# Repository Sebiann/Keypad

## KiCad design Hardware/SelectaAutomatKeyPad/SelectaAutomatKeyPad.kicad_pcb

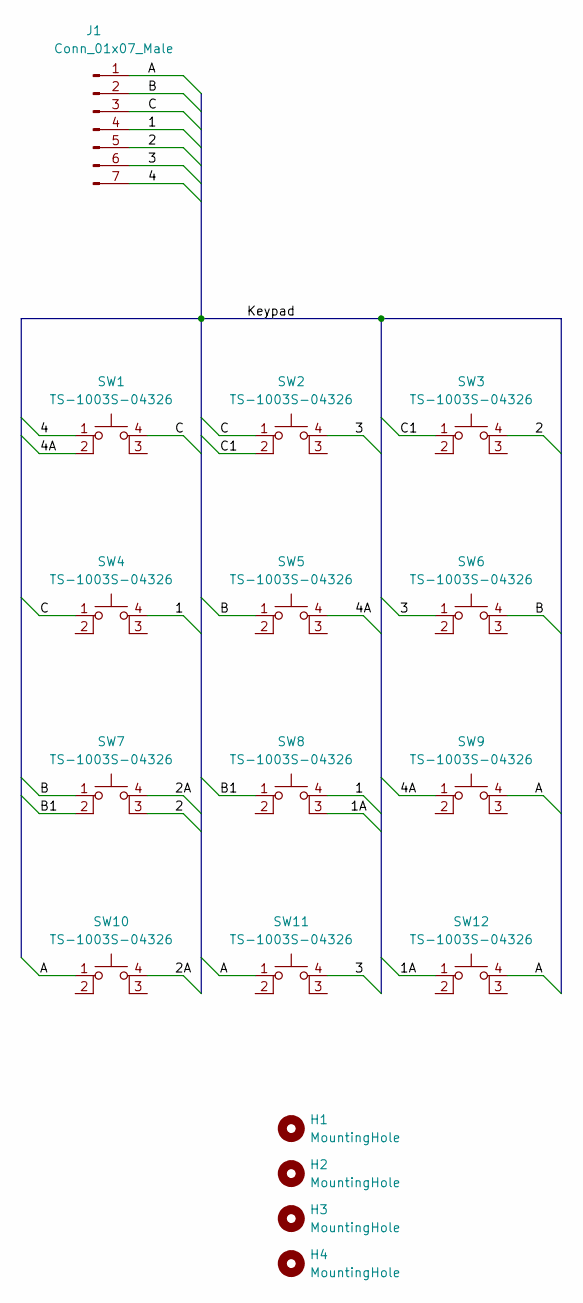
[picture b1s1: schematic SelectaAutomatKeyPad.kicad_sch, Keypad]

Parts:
H1, H2, H3, H4: MountingHole; MountingHole_2.1mm
J1: Conn_01x07_Male; PinHeader_1x07_P2.54mm_Horizontal
SW1, SW2, SW3, SW4, SW5, SW6, SW7, SW8, SW9, SW10, SW11, SW12: TS-1003S-04326; TS-1003S

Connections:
/1: J1.4, SW4.4 (A), SW8.4 (A)
/1A: SW8.3 (K), SW12.1
/2: J1.5, SW3.4 (A), SW7.3 (K)
/2A: SW7.4 (A), SW10.4 (A)
/3: J1.6, SW2.4 (A), SW6.1, SW11.4 (A)
/4: J1.7, SW1.1
/4A: SW1.2, SW5.4 (A), SW9.1
/A: J1.1, SW9.4 (A), SW10.1, SW11.1, SW12.4 (A)
/B: J1.2, SW5.1, SW6.4 (A), SW7.1
/B1: SW7.2, SW8.1
/C: J1.3, SW1.4 (A), SW2.1, SW4.1
/C1: SW2.2, SW3.1

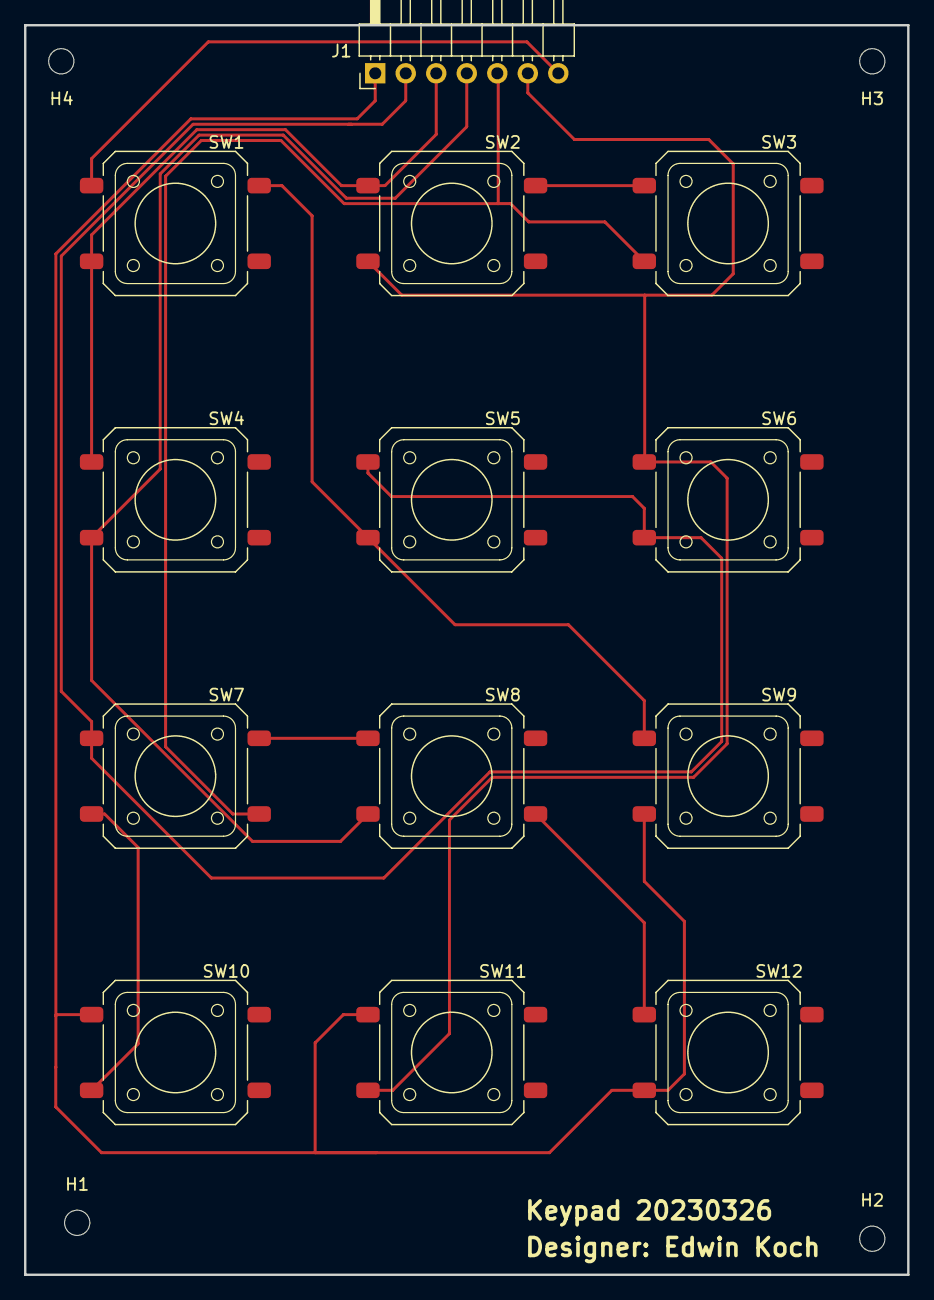
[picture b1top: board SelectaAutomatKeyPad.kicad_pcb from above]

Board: 2 copper layers, 73.5 x 104.0 mm, 17 parts (0 on the bottom side), 12 nets.

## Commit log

2023-03-03 started with schema
2023-03-04 work on layout
2023-03-06 wotk on lyout + doku
2023-03-26 created gerberfiles
2023-03-26 added .gitignore
2023-03-26 updated .gitignore
2023-03-26 changed .gitignore location
2023-03-26 removed backups
